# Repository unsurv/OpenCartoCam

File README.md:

# OpenCartoCam

## What is it

OpenCartoCam is an open source 360-degree camera that leverages edge computing to support cartographing the world. Equipped with precise positioning systems and hardware-accelerated object detection, it enables semi-automatic mapping and categorization while maintaining a compact form factor.

## Current status

Status **in development**

- decided on SolidRun [Hailo-15-SOM](https://www.solid-run.com/hailo-15-som/) as main compute unit.
- custom designed carrier board with necessary power structure and external connectors (USB, Micro SD, SMA)
- ublox NEO-F10 GNSS receiver (L1 + L5) with passive omnidirectional antenna for good value urban performance.
- two IMX 678 (M12 lens mount) sensors with kernel support
- dead reckoning
- off the shelf [Insta360 Ace Pro 2 battery](https://store.insta360.com/en/product/ace-pro-2-battery)

## TODOs

- board evaluation
- Yocto software integration
- Sensor integration (Gyro, GNSS)

## Funding

This project is funded through [NGI0 Commons Fund](https://nlnet.nl/commonsfund), a fund established by [NLnet](https://nlnet.nl) with financial support from the European Commission's [Next Generation Internet](https://ngi.eu) program. Learn more at the [NLnet project page](https://nlnet.nl/project/OpenCartoCam).

## Licences

GNSS schematic partially based on [SparkFun NEO-F10N](https://github.com/sparkfun/SparkFun_u-blox_NEO-F10N)
by SparkFun Electronics, licensed under [CC BY-SA 4.0](https://creativecommons.org/licenses/by-sa/4.0/).

Modifications by Martin. Schematic is also licensed under CC BY-SA 4.0.

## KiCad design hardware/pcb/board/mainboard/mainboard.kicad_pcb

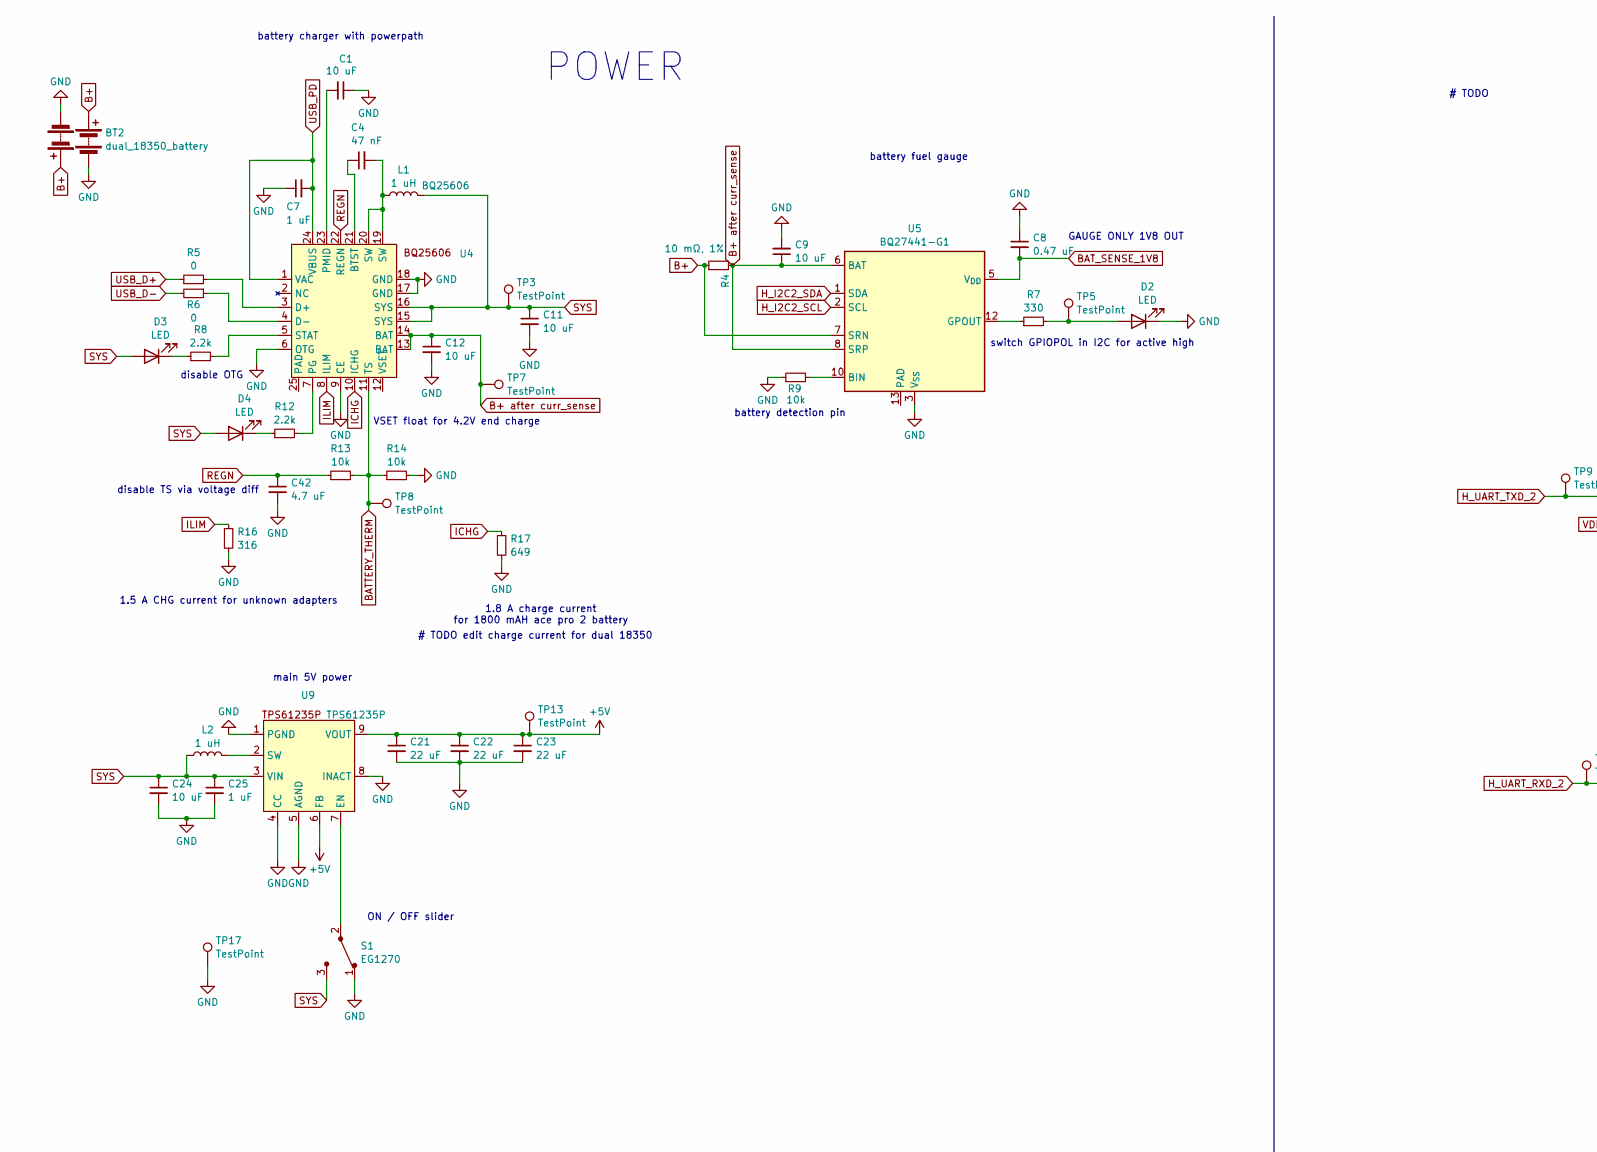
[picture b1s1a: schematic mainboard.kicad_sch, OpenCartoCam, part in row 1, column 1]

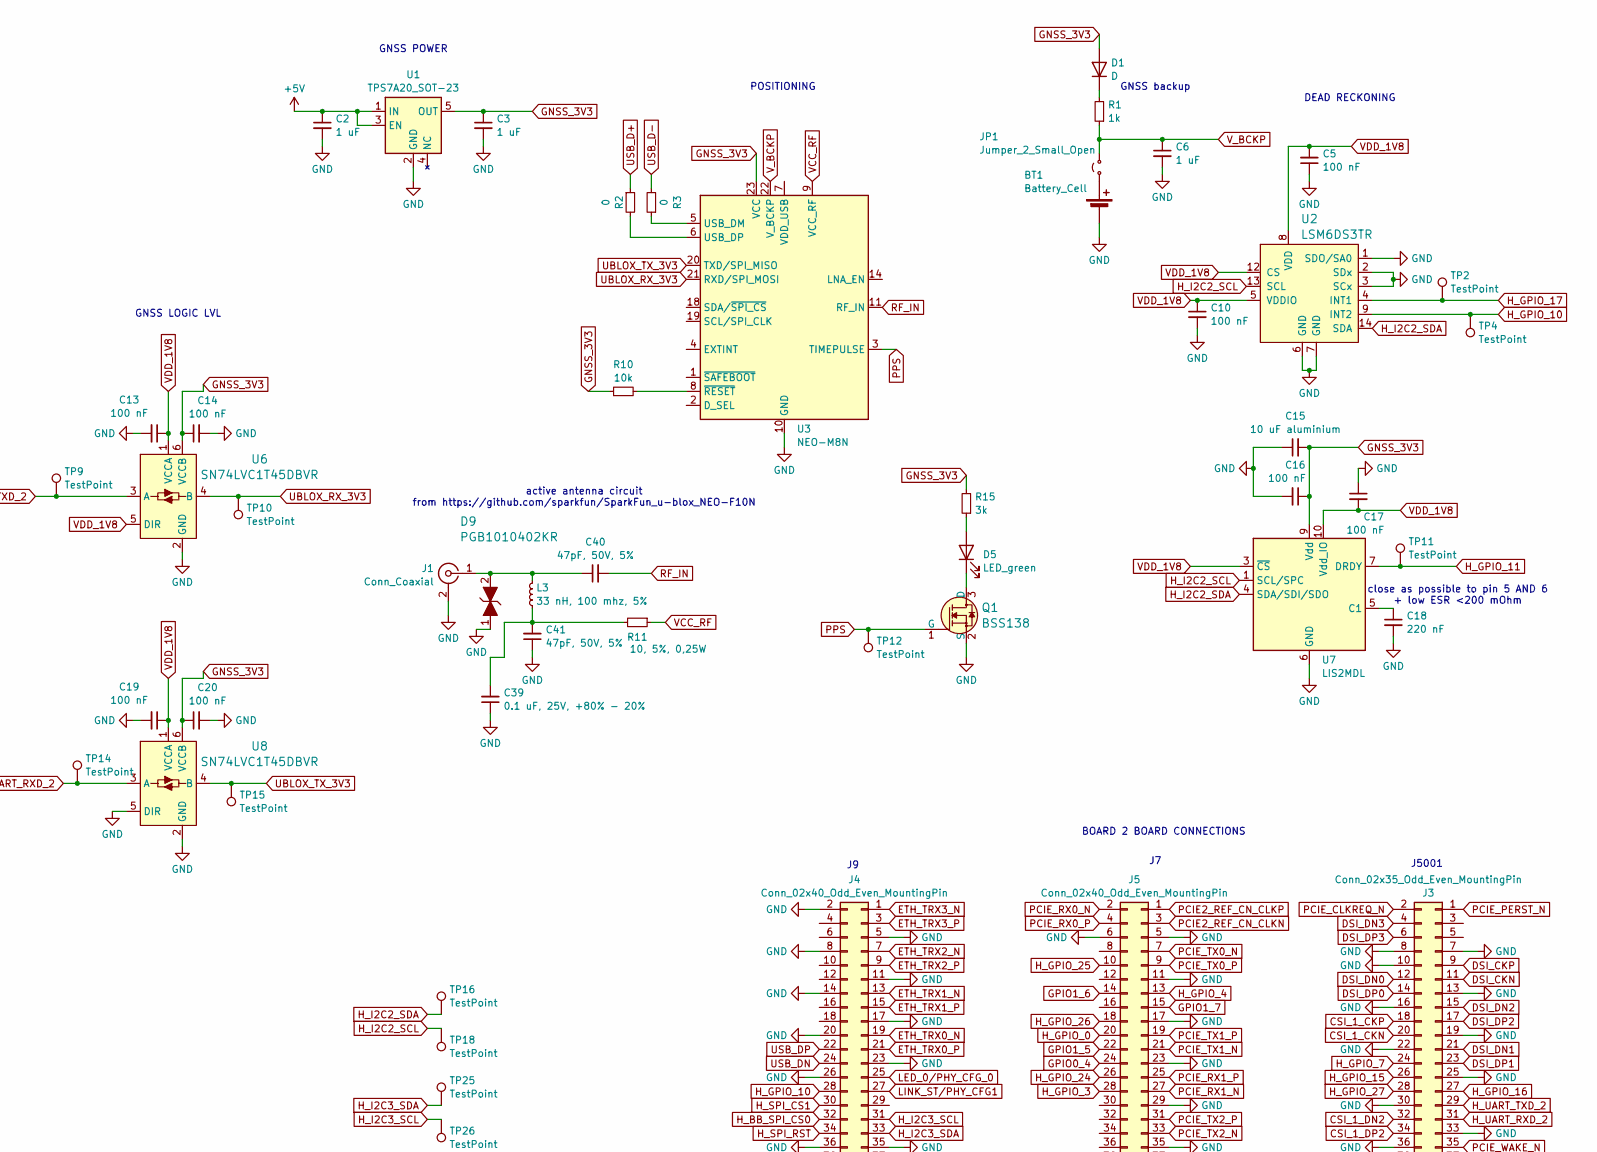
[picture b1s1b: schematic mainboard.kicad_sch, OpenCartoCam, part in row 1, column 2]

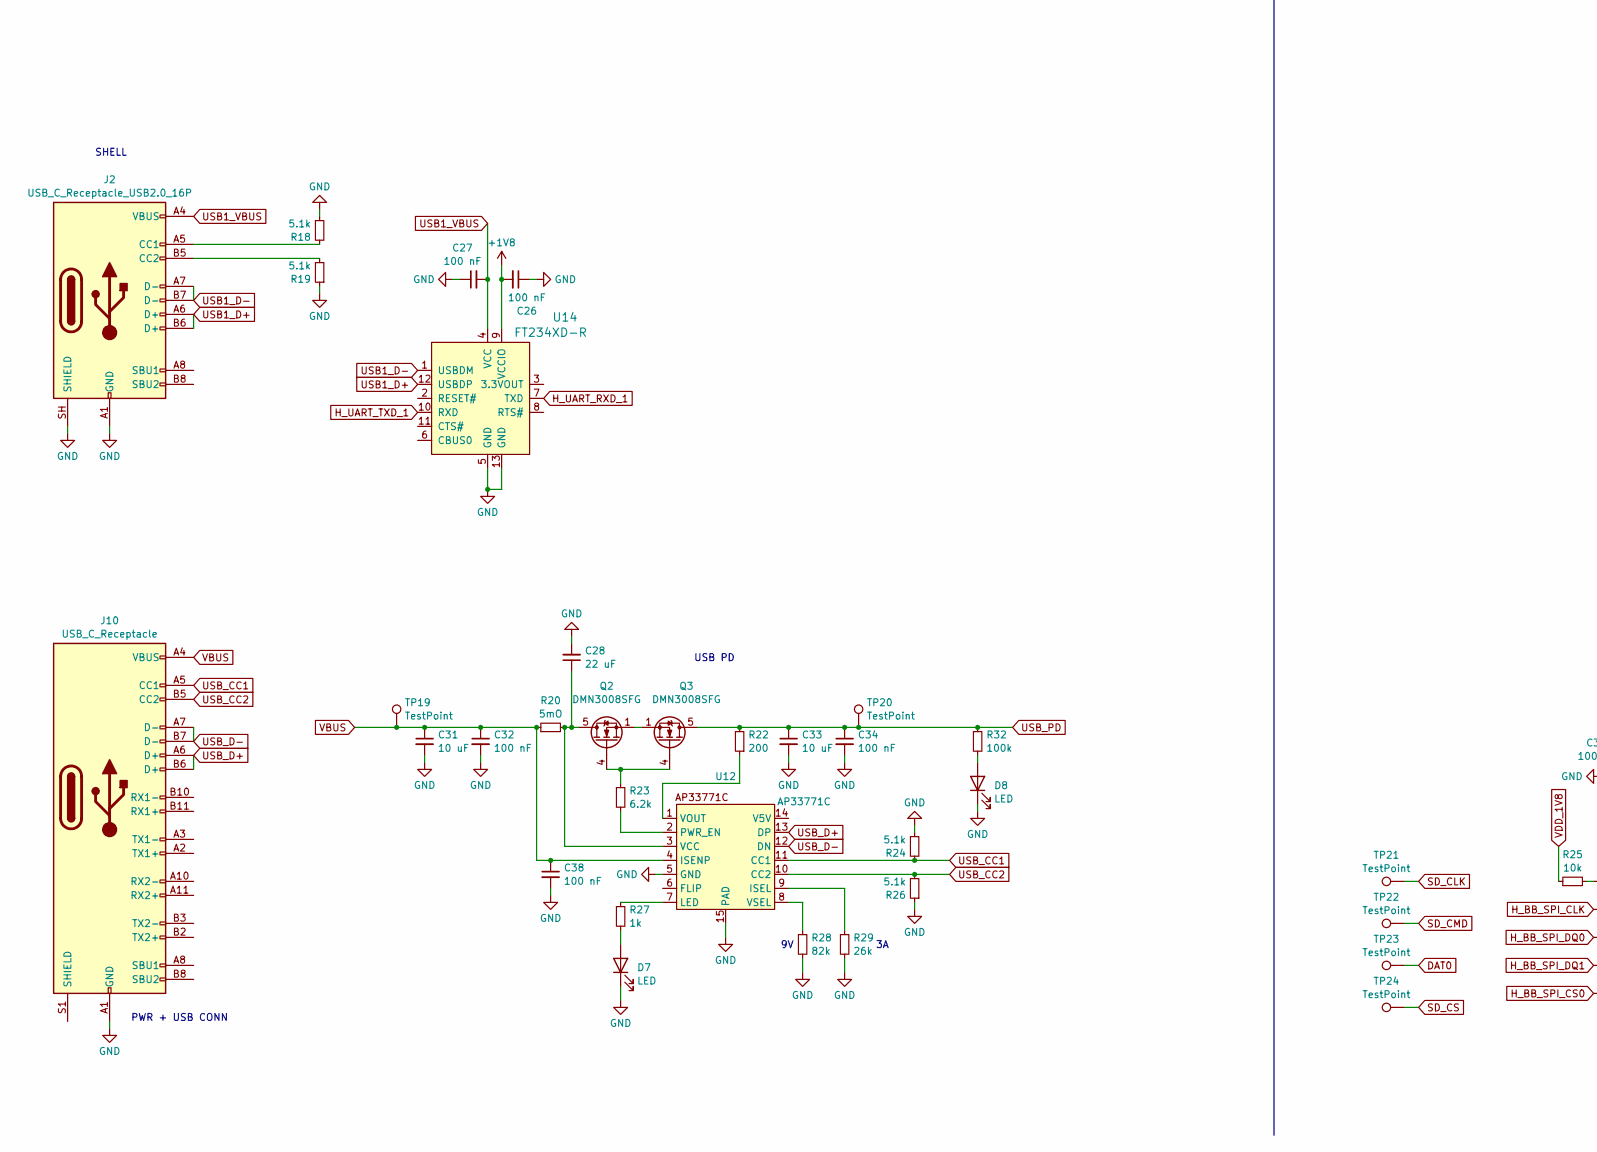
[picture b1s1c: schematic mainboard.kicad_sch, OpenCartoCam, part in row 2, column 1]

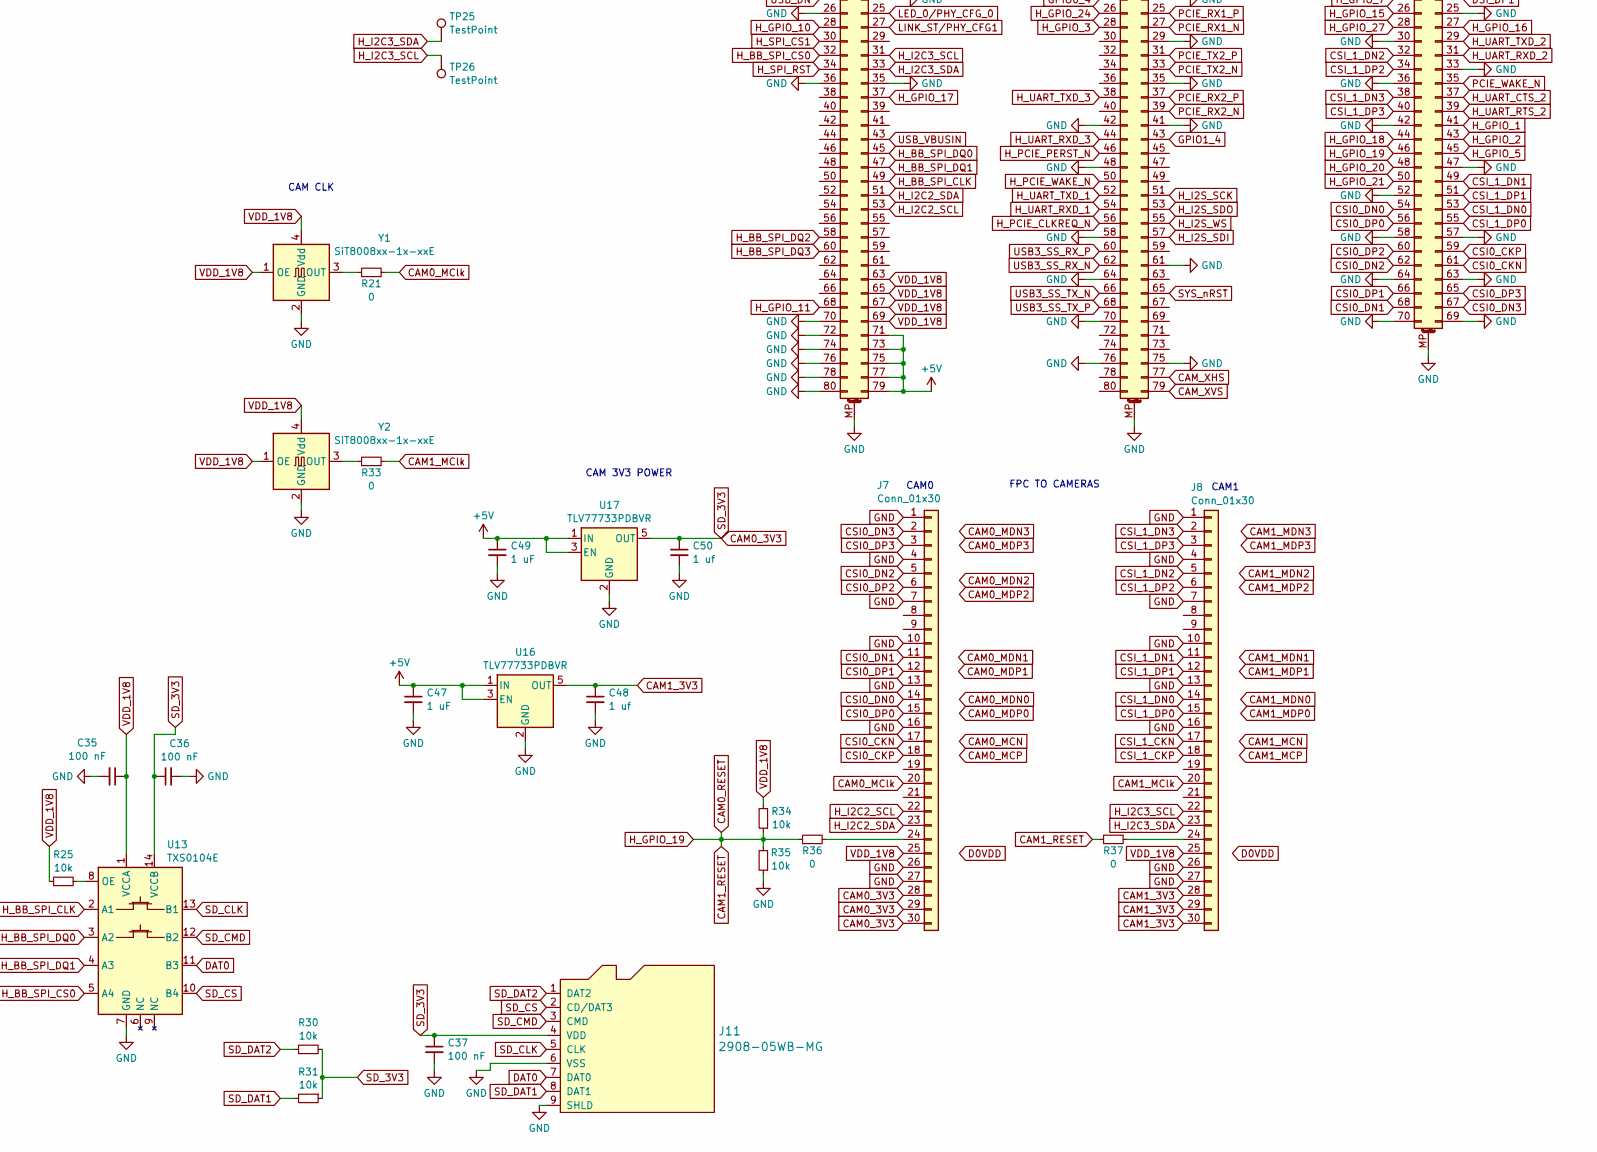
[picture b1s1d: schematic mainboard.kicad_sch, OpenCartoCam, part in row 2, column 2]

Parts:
BT1: Battery_Cell; BatteryHolder_Keystone_2998_1x6.8mm
BT2: dual_18350_battery; keystone_dual_18350
C1, C9, C11, C12, C24, C31, C33: 10 uF; C_0603_1608Metric
C2, C3, C6, C7, C25, C47, C49: 1 uF; C_0603_1608Metric
C4: 47 nF; C_0603_1608Metric
C5, C10, C13, C14, C16, C17, C19, C20, C26, C27, C32, C34, C35, C36, C37, C38: 100 nF; C_0603_1608Metric
C8: 0.47 uF; C_0603_1608Metric
C15: 10 uF aluminium; C_0603_1608Metric
C18: 220 nF; C_0603_1608Metric
C21, C22, C23, C28: 22 uF; C_0603_1608Metric
C39: 0.1 uF, 25V, +80% - 20%; C_0603_1608Metric
C40, C41: 47pF, 50V, 5%; C_0603_1608Metric
C42: 4.7 uF; C_0603_1608Metric
C48, C50: 1 uf; C_0603_1608Metric
D1: D; D_0603_1608Metric
D2, D3, D4, D7, D8: LED; LED_0603_1608Metric
D5: LED_green; LED_0603_1608Metric
D9: PGB1010402KR; D_0402_1005Metric; MPN PGB1010603MR; Digi-Key_PN F2594CT-ND
J1: Conn_Coaxial; RF_SMA_Receptical_Vertical_CONSMA002-SMD-G
J2: USB_C_Receptacle_USB2.0_16P; 2171820001_USB_C_MOLEX
J3: Conn_02x35_Odd_Even_MountingPin; DF40_3.0_70
J4, J5: Conn_02x40_Odd_Even_MountingPin; DF40_3.0_80
J7, J8: Conn_01x30; Hirose_FH12-30S-0.5SH_1x30-1MP_P0.50mm_Horizontal
J10: USB_C_Receptacle; USB_C_CONN_1054550101_MOL
J11: 2908-05WB-MG; MicroSD_2908-05WB-MG; MPN 2908-05WB-MG; Digi-Key_PN 3M5607CT-ND
JP1: Jumper_2_Small_Open; SolderJumper-2_P1.3mm_Open_TrianglePad1.0x1.5mm
L1: 1 uH; Inductor_Wuerth_74437321010
L2: 1 uH; L_Coilcraft_XAL5020-XXX
L3: 33 nH, 100 mhz, 5%; L_0402_1005Metric
Q1: BSS138; SOT-23-3; MPN BSS138; Digi-Key_PN BSS138CT-ND
Q2, Q3: DMN3008SFG; Diodes_PowerDI3333-8
R1, R27: 1k; R_0603_1608Metric
R2, R3, R5, R6, R21, R33, R36, R37: 0; R_0603_1608Metric
R4: 10 mΩ, 1%; R_0603_1608Metric
R7: 330; R_0603_1608Metric
R8, R12: 2.2k; R_0603_1608Metric
R9, R10, R13, R14, R25, R30, R31, R34, R35: 10k; R_0603_1608Metric
R11: 10, 5%, 0,25W; R_0603_1608Metric
R15: 3k; R_0603_1608Metric
R16: 316; R_0603_1608Metric
R17: 649; R_0603_1608Metric
R18, R19, R24, R26: 5.1k; R_0603_1608Metric
R20: 5mO; R_0603_1608Metric
R22: 200; R_0603_1608Metric
R23: 6.2k; R_0603_1608Metric
R28: 82k; R_0603_1608Metric
R29: 26k; R_0603_1608Metric
R32: 100k; R_0603_1608Metric
S1: EG1270; EG1270 switch; MPN EG1218; Digi-Key_PN EG1903-ND
TP2, TP3, TP4, TP5, TP7, TP8, TP9, TP10, TP11, TP12, TP13, TP14, TP15, TP16, TP17, TP18, TP19, TP20, TP21, TP22, TP23, TP24, TP25, TP26: TestPoint; TestPoint_Pad_D1.5mm
U1: TPS7A20_SOT-23; Texas_X2SON-4_1x1mm_P0.65mm
U2: LSM6DS3TR; LGA-14L_2.5x3mm__LSM6DS3; MPN LSM6DS3TR; Digi-Key_PN 497-15383-1-ND
U3: NEO-M8N; ublox_NEO
U4: BQ25606; HVQFN-24-1EP_4x4mm_P0.5mm_EP2.6x2.6mm_0.25drill_ThermalVias
U5: BQ27441-G1; Texas_S-PDSO-N12
U6, U8: SN74LVC1T45DBVR; SOT-23-6; MPN SN74LVC1T45DBVR; Digi-Key_PN 296-16843-1-ND
U7: LIS2MDL; LGA-12_2x2mm_P0.5mm
U9: TPS61235P; cursed_TI-QFN9_TPS61235
U12: AP33771C; DFN-14-1EP_3x3mm_P0.4mm_EP1.80x2.70mm
U13: TXS0104E; Texas_S-PVQFN-N14
U14: FT234XD-R; DFN-12-1EP_3x3mm; MPN FT234XD-R; Digi-Key_PN 768-1178-1-ND
U16, U17: TLV77733PDBVR; SOT-23-5
Y1, Y2: SiT8008xx-1x-xxE; Oscillator_SMD_SiT_PQFN-4Pin_2.5x2.0mm

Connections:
+1V8: C26.2, U14.9 (VCCIO)
+5V: C2.1, C21.1, C22.1, C23.1, C47.1, C49.1, J4.71, J4.73, J4.75, J4.77, J4.79, TP13.1 (1_1), U1.1 (IN), U1.3 (EN), U9.6 (FB), U9.9 (VOUT), U16.1 (IN), U16.3 (EN), U17.1 (IN), U17.3 (EN)
B+: BT2.1 (+), R4.1, U5.7 (SRN)
B+ after curr_sense: C9.1, C12.1, R4.2, TP7.1 (1_1), U4.13 (BAT), U4.14 (BAT), U5.6 (BAT), U5.8 (SRP)
BATTERY_THERM: R13.2, R14.1, TP8.1 (1_1), U4.11 (TS)
BAT_SENSE_1V8: C8.2, U5.5 (V_{DD})
CAM0_3V3: C36.1, C37.1, C50.1, J7.28, J7.29, J7.30, J11.4 (VDD), R30.2, R31.1, U13.14 (VCCB), U17.5 (OUT)
CAM0_MClk: J7.20, R21.2
CAM0_RESET: J3.46, R34.1, R35.2, R36.1, R37.1
CAM1_3V3: C48.1, J8.28, J8.29, J8.30, U16.5 (OUT)
CAM1_MClk: J8.20, R33.2
CAM_XHS: J5.77
CAM_XVS: J5.79
CSI0_CKN: J3.61, J7.17
CSI0_CKP: J3.59, J7.18
CSI0_DN0: J3.54, J7.14
CSI0_DN1: J3.68, J7.11
CSI0_DN2: J3.62, J7.5
CSI0_DN3: J3.67, J7.2
CSI0_DP0: J3.56, J7.15
CSI0_DP1: J3.66, J7.12
CSI0_DP2: J3.60, J7.6
CSI0_DP3: J3.65, J7.3
CSI_1_CKN: J3.20, J8.17
CSI_1_CKP: J3.18, J8.18
CSI_1_DN0: J3.53, J8.14
CSI_1_DN1: J3.49, J8.11
CSI_1_DN2: J3.32, J8.5
CSI_1_DN3: J3.38, J8.2
CSI_1_DP0: J3.55, J8.15
CSI_1_DP1: J3.51, J8.12
CSI_1_DP2: J3.34, J8.6
CSI_1_DP3: J3.40, J8.3
DAT0: J11.7 (DAT0), TP23.1 (1_1), U13.11 (B3)
DSI_CKN: J3.11
DSI_CKP: J3.9
DSI_DN0: J3.12
DSI_DN1: J3.21
DSI_DN2: J3.15
DSI_DN3: J3.4
DSI_DP0: J3.14
DSI_DP1: J3.23
DSI_DP2: J3.17
DSI_DP3: J3.6
ETH_TRX0_N: J4.19
ETH_TRX0_P: J4.21
ETH_TRX1_N: J4.13
ETH_TRX1_P: J4.15
ETH_TRX2_N: J4.7
ETH_TRX2_P: J4.9
ETH_TRX3_N: J4.1
ETH_TRX3_P: J4.3
GND: BT1.2 (-), BT2.2 (-), C1.1, C2.2, C3.2, C5.1, C6.2, C7.1, C8.1, C9.2, C10.2, C11.2, C12.2, C13.2, C14.2, C15.1, C16.2, C17.1, C18.2, C19.2, C20.2, C21.2, C22.2, C23.2, C24.2, C25.2, C26.1, C27.1, C28.2, C31.2, C32.2, C33.2, C34.2, C35.2, C36.2, C37.2, C38.2, C39.1, C41.1, C42.2, C47.2, C48.2, C49.2, C50.2, D2.1 (K), D7.1 (K), D8.1 (K), D9.1, J1.2 (Ext), J2.A1 (GND), J2.A12 (GND), J2.B1 (GND), J2.B12 (GND), J2.SH (SHIELD), J3.7, J3.8, J3.10, J3.13, J3.16, J3.19, J3.22, J3.25, J3.30, J3.33, J3.36, J3.42, J3.47, J3.52, J3.57, J3.58, J3.63, J3.64, J3.69, J3.70, J3.MP (MountPin), J4.2, J4.5, J4.8, J4.11, J4.14, J4.17, J4.20, J4.23, J4.26, J4.35, J4.36, J4.70, J4.72, J4.74, J4.76, J4.78, J4.80, J4.MP (MountPin), J5.5, J5.6, J5.11, J5.17, J5.23, J5.29, J5.35, J5.41, J5.42, J5.48, J5.58, J5.61, J5.64, J5.70, J5.75, J5.76, J5.MP (MountPin), J7.1, J7.4, J7.7, J7.10, J7.13, J7.16, J7.26, J7.27, J8.1, J8.4, J8.7, J8.10, J8.13, J8.16, J8.26, J8.27, J10.A1 (GND), J10.A12 (GND), J10.B1 (GND), J10.B12 (GND), J11.6 (VSS), J11.9 (SHLD), Q1.2 (S), R9.1, R14.2, R16.2, R17.2, R18.1, R19.1, R24.1, R26.1, R28.2, R29.2, R35.1, S1.1, TP17.1 (1_1), U1.2 (GND), U2.1 (SDO/SA0), U2.2 (SDx), U2.3 (SCx), U2.6 (GND), U2.7 (GND), U3.10 (GND), U3.12 (GND), U3.13 (GND), U3.24 (GND), U4.6 (OTG), U4.9 (CE), U4.17 (GND), U4.18 (GND), U5.3 (V_{SS}), U6.2 (GND), U7.6 (GND), U7.8 (GND), U8.2 (GND), U8.5 (DIR), U9.1 (PGND), U9.4 (CC), U9.5 (AGND), U9.8 (INACT), U12.5 (GND), U12.15 (PAD), U13.7 (GND), U14.5 (GND), U14.13 (GND), U16.2 (GND), U17.2 (GND), Y1.2 (GND), Y2.2 (GND)
GNSS_3V3: C3.1, C14.1, C15.2, C16.1, C20.1, D1.2 (A), R10.1, R15.2, U1.5 (OUT), U3.23 (VCC), U6.6 (VCCB), U7.9 (Vdd), U8.6 (VCCB)
GPIO0_4: J5.24
GPIO1_4: J5.43
GPIO1_5: J5.22
GPIO1_6: J5.14
GPIO1_7: J5.15
H_BB_SPI_CLK: J4.49, U13.2 (A1)
H_BB_SPI_CS0: J4.32, U13.5 (A4)
H_BB_SPI_DQ0: J4.45, U13.3 (A2)
H_BB_SPI_DQ1: J4.47, U13.4 (A3)
H_BB_SPI_DQ2: J4.58
H_BB_SPI_DQ3: J4.60
H_GPIO_0: J5.20
H_GPIO_1: J3.41
H_GPIO_2: J3.43
H_GPIO_3: J5.28
H_GPIO_4: J5.13
H_GPIO_5: J3.45
H_GPIO_7: J3.24
H_GPIO_10: J4.28, TP4.1 (1_1), U2.9 (INT2)
H_GPIO_11: J4.68, TP11.1 (1_1), U7.7 (DRDY)
H_GPIO_15: J3.26
H_GPIO_16: J3.27
H_GPIO_17: J4.37, TP2.1 (1_1), U2.4 (INT1)
H_GPIO_18: J3.44
H_GPIO_20: J3.48
H_GPIO_21: J3.50
H_GPIO_24: J5.26
H_GPIO_25: J5.10
H_GPIO_26: J5.18
H_GPIO_27: J3.28
H_I2C2_SCL: J4.53, J7.22, TP18.1 (1_1), U2.13 (SCL), U5.2 (SCL), U7.1 (SCL/SPC)
H_I2C2_SDA: J4.51, J7.23, TP16.1 (1_1), U2.14 (SDA), U5.1 (SDA), U7.4 (SDA/SDI/SDO)
H_I2C3_SCL: J4.31, J8.22, TP26.1 (1_1)
H_I2C3_SDA: J4.33, J8.23, TP25.1 (1_1)
H_I2S_SCK: J5.51
H_I2S_SDI: J5.57
H_I2S_SDO: J5.53
H_I2S_WS: J5.55
H_PCIE_CLKREQ_N: J5.56
H_PCIE_PERST_N: J5.46
H_PCIE_WAKE_N: J5.50
H_SPI_CS1: J4.30
H_SPI_RST: J4.34
H_UART_CTS_2: J3.37
H_UART_RTS_2: J3.39
H_UART_RXD_1: J5.54, U14.7 (TXD)
H_UART_RXD_2: J3.31, TP14.1 (1_1), U8.3 (A)
H_UART_RXD_3: J5.44
H_UART_TXD_1: J5.52, U14.10 (RXD)
H_UART_TXD_2: J3.29, TP9.1 (1_1), U6.3 (A)
H_UART_TXD_3: J5.38
ICHG: R17.1, U4.10 (ICHG)
ILIM: R16.1, U4.8 (ILIM)
LED_0/PHY_CFG_0: J4.25
LINK_ST/PHY_CFG1: J4.27
unnamed: BT1.1 (+), JP1.1 (A)
unnamed: C4.2, L1.1, U4.19 (SW), U4.20 (SW)
unnamed: C39.2, C41.2, L3.1, R11.2
unnamed: D1.1 (K), R1.2
unnamed: D2.2 (A), R7.2, TP5.1 (1_1)
unnamed: D3.1 (K), R8.1
unnamed: D4.1 (K), R12.1
unnamed: D5.2 (A), R15.1
unnamed: D5.1 (K), Q1.3 (D)
unnamed: D7.2 (A), R27.2
unnamed: D8.2 (A), R32.2
unnamed: C40.1, D9.2, J1.1 (In), L3.2
unnamed: J2.A5 (CC1), R18.2
unnamed: J2.B5 (CC2), R19.2
unnamed: J7.24, R36.2
unnamed: J8.24, R37.2
unnamed: C28.1, Q2.5 (D), R20.2, U12.3 (VCC)
unnamed: Q2.4 (G), Q3.4 (G), R23.1
unnamed: Q2.1 (S), Q2.2 (S), Q2.3 (S), Q3.1 (S), Q3.2 (S), Q3.3 (S)
unnamed: R3.1, U3.5 (USB_DM)
unnamed: R2.2, U3.6 (USB_DP)
unnamed: R10.2, U3.8 (~RESET)
unnamed: C4.1, U4.21 (BTST)
unnamed: R5.2, U4.3 (D+)
unnamed: R6.1, U4.4 (D-)
unnamed: R12.2, U4.7 (PG)
unnamed: C1.2, U4.23 (PMID)
unnamed: R8.2, U4.5 (STAT)
unnamed: R9.2, U5.10 (BIN)
unnamed: R7.1, U5.12 (GPOUT)
unnamed: C18.1, U7.5 (C1)
unnamed: S1.2, U9.7 (EN)
unnamed: L2.2, U9.2 (SW)
unnamed: R29.1, U12.9 (ISEL)
unnamed: R27.1, U12.7 (LED)
unnamed: R23.2, U12.2 (PWR_EN)
unnamed: R22.1, U12.1 (VOUT)
unnamed: R28.1, U12.8 (VSEL)
unnamed: R25.2, U13.8 (OE)
unnamed: R21.1, Y1.3 (OUT)
unnamed: R33.1, Y2.3 (OUT)
PCIE2_REF_CN_CLKN: J5.3
PCIE2_REF_CN_CLKP: J5.1
PCIE_CLKREQ_N: J3.2
PCIE_PERST_N: J3.1
PCIE_RX0_N: J5.2
PCIE_RX0_P: J5.4
PCIE_RX1_N: J5.27
PCIE_RX1_P: J5.25
PCIE_RX2_N: J5.39
PCIE_RX2_P: J5.37
PCIE_TX0_N: J5.7
PCIE_TX0_P: J5.9
PCIE_TX1_N: J5.21
PCIE_TX1_P: J5.19
PCIE_TX2_N: J5.33
PCIE_TX2_P: J5.31
PCIE_WAKE_N: J3.35
PPS: Q1.1 (G), TP12.1 (1_1), U3.3 (TIMEPULSE)
REGN: C42.1, R13.1, U4.22 (REGN)
RF_IN: C40.2, U3.11 (RF_IN)
SD_CLK: J11.5 (CLK), TP21.1 (1_1), U13.13 (B1)
SD_CMD: J11.3 (CMD), TP22.1 (1_1), U13.12 (B2)
SD_CS: J11.2 (CD/DAT3), TP24.1 (1_1), U13.10 (B4)
SD_DAT1: J11.8 (DAT1), R31.2
SD_DAT2: J11.1 (DAT2), R30.1
SYS: C11.1, C24.1, C25.1, D3.2 (A), D4.2 (A), L1.2, L2.1, S1.3, TP3.1 (1_1), U4.15 (SYS), U4.16 (SYS), U9.3 (VIN)
SYS_nRST: J5.65
UBLOX_RX_3V3: TP10.1 (1_1), U3.21 (RXD/SPI_MOSI), U6.4 (B)
UBLOX_TX_3V3: TP15.1 (1_1), U3.20 (TXD/SPI_MISO), U8.4 (B)
USB1_D+: J2.A6 (D+), J2.B6 (D+), U14.12 (USBDP)
USB1_D-: J2.A7 (D-), J2.B7 (D-), U14.1 (USBDM)
USB1_VBUS: C27.2, J2.A4 (VBUS), J2.A9 (VBUS), J2.B4 (VBUS), J2.B9 (VBUS), U14.4 (VCC)
USB3_SS_RX_N: J5.62
USB3_SS_RX_P: J5.60
USB3_SS_TX_N: J5.66
USB3_SS_TX_P: J5.68
USB_CC1: J10.A5 (CC1), R24.2, U12.11 (CC1)
USB_CC2: J10.B5 (CC2), R26.2, U12.10 (CC2)
USB_D+: J10.A6 (D+), J10.B6 (D+), R2.1, R5.1, U12.13 (DP)
USB_D-: J10.A7 (D-), J10.B7 (D-), R3.2, R6.2, U12.12 (DN)
USB_DN: J4.24
USB_DP: J4.22
USB_PD: C7.2, C33.1, C34.1, Q3.5 (D), R22.2, R32.1, TP20.1 (1_1), U4.1 (VAC), U4.24 (VBUS)
USB_VBUSIN: J4.43
VBUS: C31.1, C32.1, C38.1, J10.A4 (VBUS), J10.A9 (VBUS), J10.B4 (VBUS), J10.B9 (VBUS), R20.1, TP19.1 (1_1), U12.4 (ISENP)
VCC_RF: R11.1, U3.9 (VCC_RF)
VDD_1V8: C5.2, C10.1, C13.1, C17.2, C19.1, C35.1, J4.63, J4.65, J4.67, J4.69, J7.25, J8.25, R25.1, R34.2, U2.5 (VDDIO), U2.8 (VDD), U2.12 (CS), U6.1 (VCCA), U6.5 (DIR), U7.3 (~CS), U7.10 (Vdd_IO), U8.1 (VCCA), U13.1 (VCCA), Y1.1 (OE), Y1.4 (Vdd), Y2.1 (OE), Y2.4 (Vdd)
V_BCKP: C6.1, JP1.2 (B), R1.1, U3.22 (V_BCKP)

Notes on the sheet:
BOARD 2 BOARD CONNECTIONS
ON / OFF slider
J5001
# TODO edit charge current for dual 18350
USB PD
CAM CLK
GNSS backup
battery detection pin
FPC TO CAMERAS
# TODO
CAM 3V3 POWER
battery charger with powerpath
main 5V power
PWR + USB CONN
close as possible to pin 5 AND 6 + low ESR <200 mOhm
disable OTG
GAUGE ONLY 1V8 OUT
GNSS POWER
POSITIONING
1.5 A CHG current for unknown adapters
POWER
disable TS via voltage diff
DEAD RECKONING
SHELL
CAM0
GNSS LOGIC LVL
switch GPIOPOL in I2C for active high
1.8 A charge current for 1800 mAH ace pro 2 battery
active antenna circuit from https://github.com/sparkfun/SparkFun_u-blox_NEO-F10N
battery fuel gauge
CAM1
VSET float for 4.2V end charge

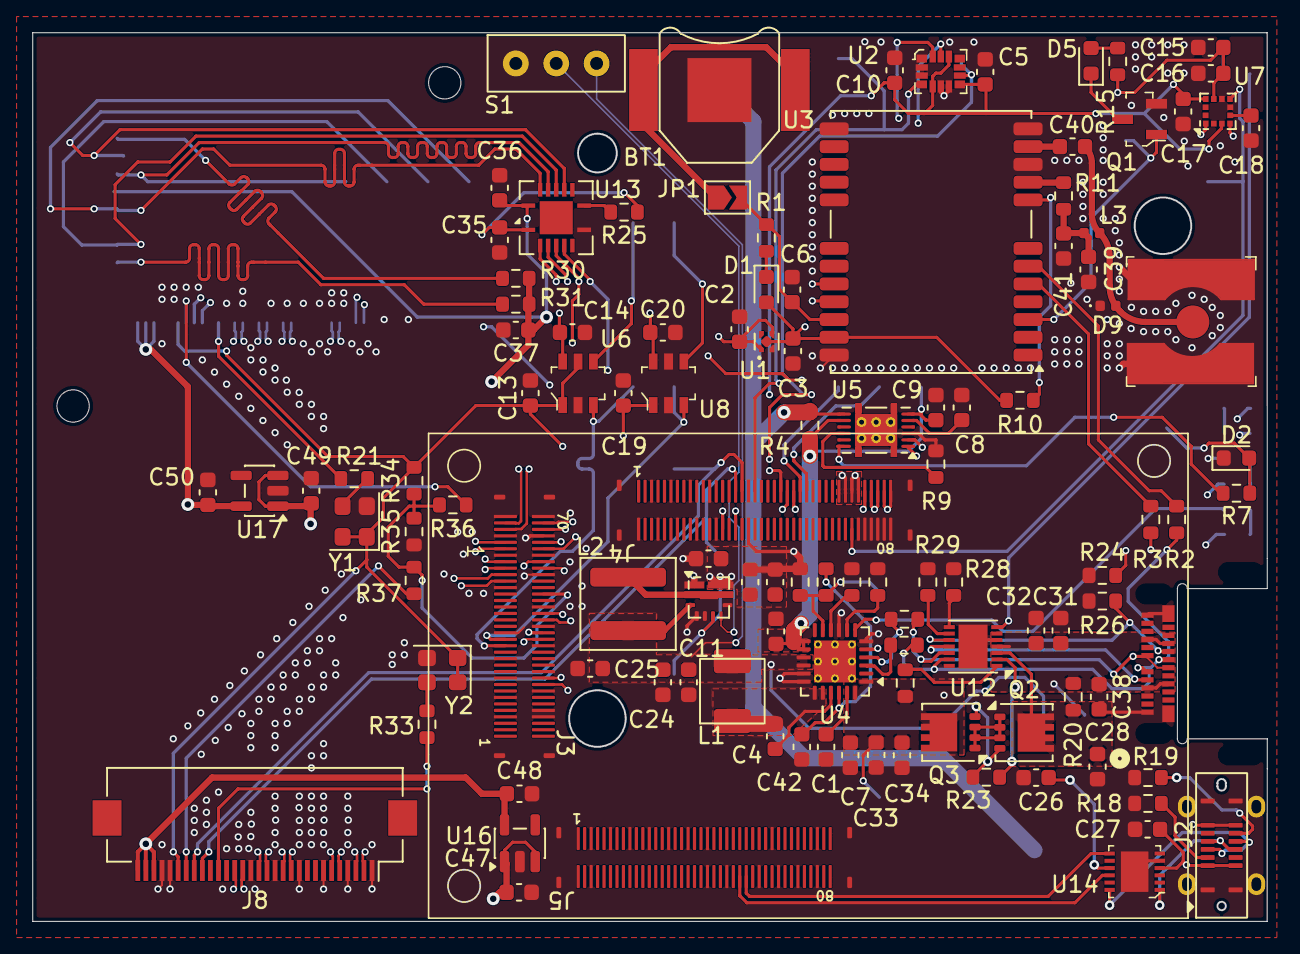
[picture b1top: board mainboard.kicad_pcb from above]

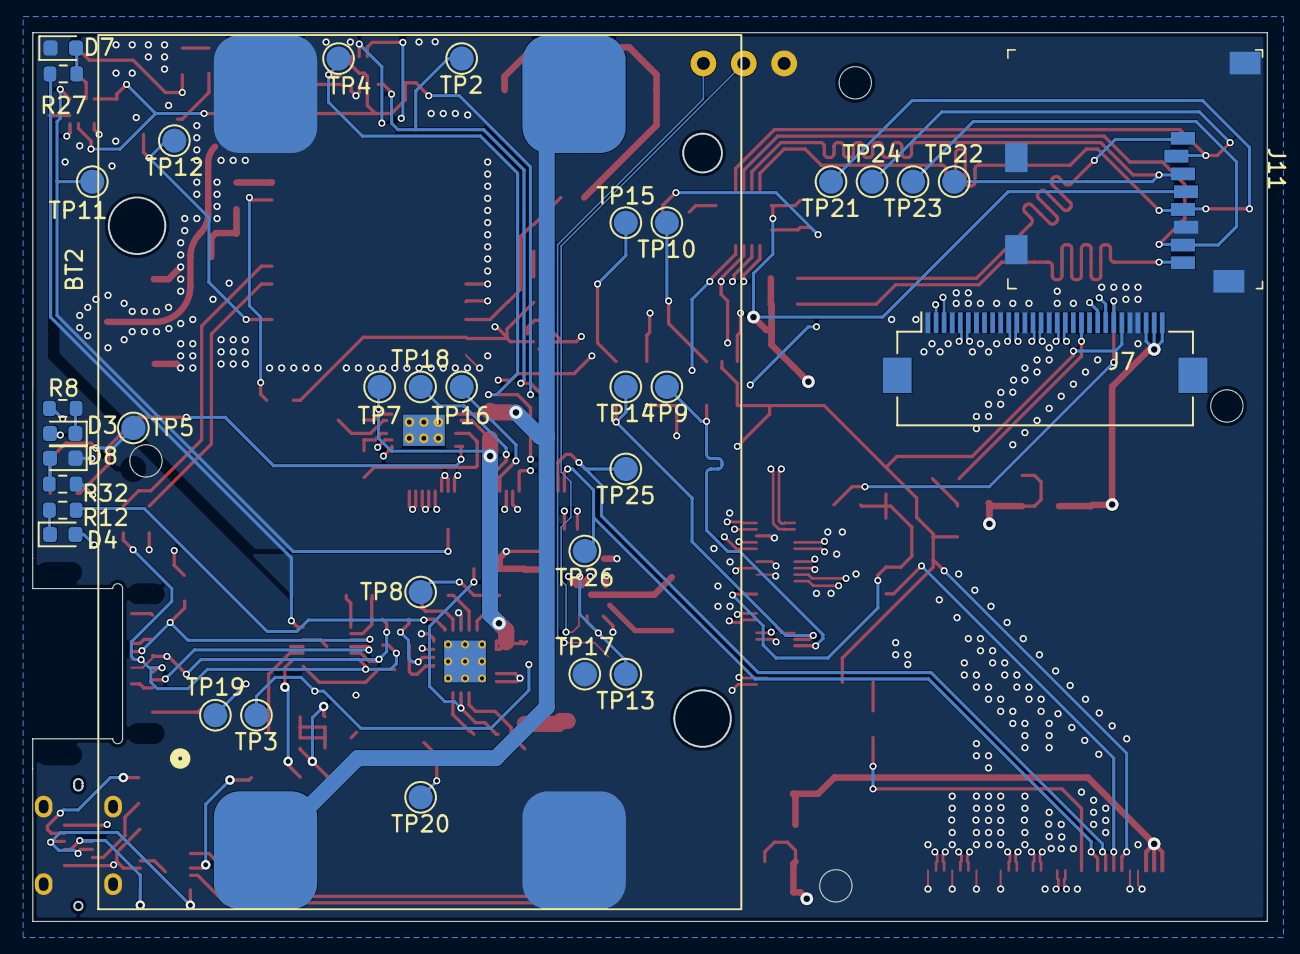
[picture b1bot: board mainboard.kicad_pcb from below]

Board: 6 copper layers, 76.4 x 55.0 mm, 148 parts (35 on the bottom side), 115 nets.

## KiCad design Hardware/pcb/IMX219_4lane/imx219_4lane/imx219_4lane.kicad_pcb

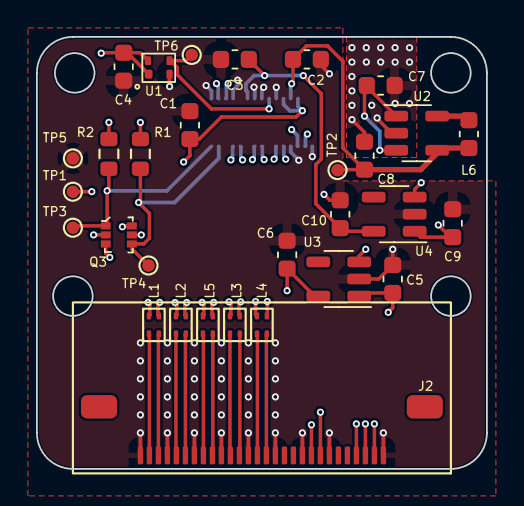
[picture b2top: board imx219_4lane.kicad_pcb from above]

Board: 4 copper layers, 25.0 x 24.0 mm, 31 parts (1 on the bottom side), 32 nets.

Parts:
C1, C2, C3, C5, C6, C9, C10: 1uF; C_0603_1608Metric
C4: 0.1uF; C_0603_1608Metric
C7: 4.7uF; C_0603_1608Metric
C8: 10uF; C_0603_1608Metric
J1: DF37NC-30DS-0.4V; DF37NC-30DS
J2: FPC 28 pin connector; Molex 505110-2891
L1, L2, L3, L4, L5: DLP11SN900HL2L; DLP11SN900HL2L_hand_solder
L6: 10uF; C_0603_1608Metric
Q3: NTZD3154N; SOT-563
R1, R2: 2K2; R_0603_1608Metric
TP1, TP2, TP3, TP4, TP5, TP6: TestPoint; TestPoint_Pad_D0.7mm
U1: AMPM; AMPM oscillator
U2: LM3670MF; SOT-23-5
U3, U4: AP7331; SOT-23-5

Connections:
+1V2: C2.1, C8.1, J1.4 (VD1V2), L6.1, TP2.1, U2.4 (FB)
+1V8: C1.1, C4.1, C6.1, J1.3 (VO1V8), J1.5 (/PWDN), Q3.2 (G2), Q3.5 (G1), R1.1, R2.1, TP1.1, U1.1 (OE), U1.4 (VDD), U3.5 (OUT)
+2V8: C3.1, C10.1, J1.10 (VA2V8), U4.5 (OUT)
+5V: C5.1, C7.1, C9.1, J2.2, J2.3, J2.4, U2.1 (Vin), U2.3 (EN), U3.1 (IN), U3.3 (EN), U4.1 (IN), U4.3 (EN)
CSI_CLKN: J1.26 (MCKN), L5.3
CSI_CLKP: J1.27 (MCKP), L5.2
CSI_D0N: J1.23 (MD0N), L4.3
CSI_D0P: J1.24 (MD0P), L4.2
CSI_D1N: J1.20 (MD1N), L3.3
CSI_D1P: J1.21 (MD1P), L3.2
CSI_D2N: J1.17 (MD2N), L2.3
CSI_D2P: J1.18 (MD2P), L2.2
CSI_D3N: J1.14 (MD3N), L1.3
CSI_D3P: J1.13 (MD3P), L1.2
GND: C1.2, C2.2, C3.2, C4.2, C5.2, C6.2, C7.2, C8.2, C9.2, C10.2, J1.6 (DGND4), J1.8 (DGND3), J1.9 (AGND), J1.12 (DGND2), J1.15 (DGND1), J1.16 (DGND5), J1.19 (DGND6), J1.22 (DGND7), J1.25 (DGND8), J1.28 (DGND9), J2.1, J2.7, J2.10, J2.13, J2.16, J2.19, J2.22, J2.25, J2.28, TP5.1, U1.2 (GND), U2.2 (GND), U3.2 (GND), U4.2 (GND)
I2C_SCL_3V3: J2.9, Q3.3 (D1)
I2C_SDA_3V3: J2.8, Q3.6 (D2)
MCLK: J1.7 (MCLK), TP6.1, U1.3 (OUT)
MIPI_CLK_N: J2.20, L5.4
MIPI_CLK_P: J2.21, L5.1
MIPI_DATA_0_N: J2.14, L4.4
MIPI_DATA_0_P: J2.15, L4.1
MIPI_DATA_1_N: J2.17, L3.4
MIPI_DATA_1_P: J2.18, L3.1
MIPI_DATA_2_N: J2.23, L2.4
MIPI_DATA_2_P: J2.24, L2.1
MIPI_DATA_3_N: J2.26, L1.4
MIPI_DATA_3_P: J2.27, L1.1
unnamed: L6.2, U2.5 (SW)
SCL_1V8: J1.29 (SCL), Q3.4 (S1), R1.2, TP4.1
SDA_1V8: J1.30 (SDA), Q3.1 (S2), R2.2, TP3.1
SHELL: J2.29, J2.30

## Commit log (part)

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2025-12-01 small docs update
2026-03-12 add basic docs
2026-03-12 add rtd config file
2026-03-12 point rtd to subdir
2026-03-12 revert to index file for rtd
2026-03-12 rework directory structure
2026-03-12 add arducam IMX219_fisheye model
2026-03-13 preliminary 3d placements
2026-03-14 update SoM model
2026-04-10 new IMX678 model
2026-04-18 initial part selection in schematic
2026-04-19 TPS61235 stable 5V schematic
2026-04-20 preliminary BQ25601D
2026-04-27 start MIPI adaption from SOM board
2026-04-28 added board to board connections for SOM
2026-04-29 add accelerometer + magnetometer default schematic
2026-04-30 preliminary FPC MIPI conn from SOM
2026-05-01 split cam connections + rotate b2b connectors
2026-05-02 place board to board connectors
2026-05-02 switch b2b connector order
2026-05-04 USB PD AP33771C
2026-05-06 increase pagesize, rework power ICs
2026-05-06 rework battery charger
2026-05-06 GNSS level shifters, corect labels, set CHG voltage + current
2026-05-06 testpoints, GNSS backup from sparkfun
2026-05-06 update b2b connector labels
2026-05-07 update docs
2026-05-07 update 3d model
2026-05-07 split docs into folders and adapt toctree
2026-05-07 FTDI IC to USB conn
2026-05-08 add SD card + separate 3V3 for GNSS IC
2026-05-08 SD pt. II
2026-05-09 TP all the things!
2026-05-09 PCB stackup
2026-05-09 update with created footprints
2026-05-09 updated battery holder for GNSS backup power
2026-05-09 add schematic as PDF
2026-05-09 generate schemati pdf in docs dir
2026-05-09 update hardware docs
2026-05-10 rough grouping of ICs on PCB
2026-05-11 assign 3D models
2026-05-11 parts placement
2026-05-12 preliminary placement of all parts
2026-05-13 replace battery with dual 18350
2026-05-13 organize PCB around new battery holder
2026-05-13 replace FTDI with DFN12 package
2026-05-15 update active antenna design
2026-05-21 docs - add targets for object detection
2026-05-21 update SMA receptable
2026-05-27 switch to vertical USB C receptable for shell
2026-05-27 length match cam0 pairs
2026-05-27 add .lck to .gitignore
2026-05-27 USB PD power
2026-05-28 BQ25606 routing
2026-05-29 TPS61235p 5v PWR routing
2026-05-31 route ublox GNSS receiver
2026-06-03 change MIPI CSI location according to new schematics
2026-06-04 new 3V3 setup for cameras, 30 pin mipi connections
2026-06-04 place ment of new 3V3 + oscillators + reset mechanic
2026-06-05 placeholder osci 3d shape
2026-06-05 cam1 MIPI pairs
2026-06-05 cam0 MIPI pairs
2026-06-06 dead reckoning routing
2026-06-06 SD card routing
2026-06-06 I2C cam0 cam1
2026-06-08 route TPs
2026-06-08 update schematic PDF
2026-06-09 zone fill clearance
2026-06-09 correct terminal USB pads
2026-06-09 silkscreen readability check
2026-06-09 5V connection to DF40
2026-06-09 fix drill sizes + add GND vias
2026-06-10 back silkscreen readability
2026-06-10 add on-off slider switch
2026-06-10 create HAILO SOM mounting holes
2026-06-10 update 3D model + add preview to docs
2026-06-10 improve schematic readability + add docstrings
2026-06-10 docs update
2026-06-11 add acknowledgement for nlnet
2026-06-15 directly include images in grant docs
2026-06-15 small typo fix
2026-06-15 fix schematic PDF location
2026-06-23 start 3d work on case
